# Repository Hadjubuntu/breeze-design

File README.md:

# breeze-design
Breeze design documents

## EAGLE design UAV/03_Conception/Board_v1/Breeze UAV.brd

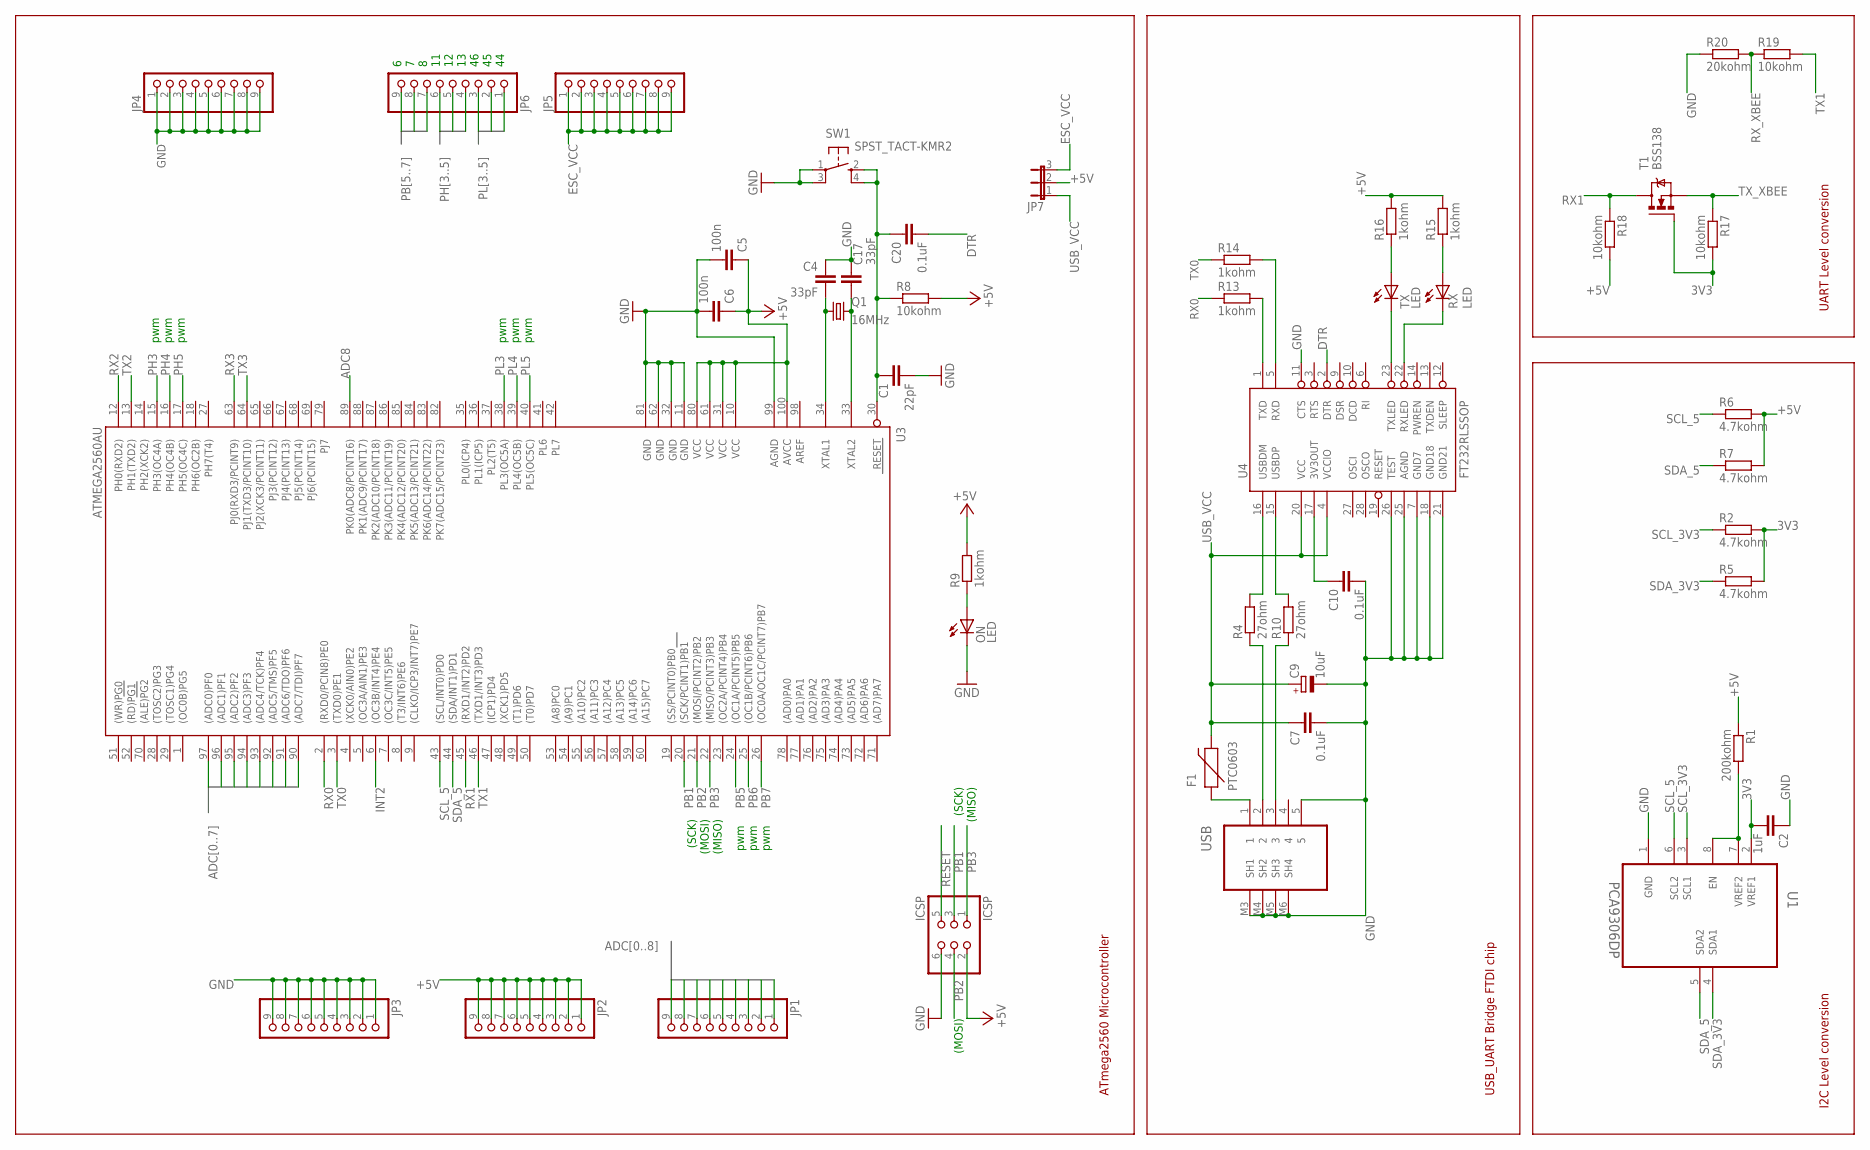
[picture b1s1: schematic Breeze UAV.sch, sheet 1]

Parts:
C1: 22pF; C0402
C2: 1uF; C0402
C4, C17: 33pF; C0402
C5, C6: 100n; C0402
C7, C10, C20: 0.1uF; C0402
C9: 10uF; SMC_A
F1: PTC0603; 0603
ICSP: ICSP; 2X03
JP1, JP2, JP3, JP4, JP5, JP6: PINHD-1X9; 1X09
JP7: JP2E; JP2
ON: LED; CHIPLED_0603
Q1: 16MHz; CTS406
R1: 200kohm; R0402
R2, R5, R6, R7: 4.7kohm; R0402
R4, R10: 27ohm; R0402
R8, R17, R18, R19: 10kohm; R0402
R9, R13, R14, R15, R16: 1kohm; R0402
R20: 20kohm; R0402
RX: LED; CHIPLED_0603
SW1: SPST_TACT-KMR2; KMR2
T1: BSS138; SOT23
TX: LED; CHIPLED_0603
U1: PCA9306DP; SOP65P490X110-8N
U3: ATMEGA2560AU; TQFP100
U4: FT232RLSSOP; SSOP28DB
USB: 47346-0001; MOLEX_47346-0001

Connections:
3V3: C2.2, R2.2, R5.2, R17.2, T1.1 (G), U1.2 (VREF1); also elsewhere on the board
+5V: C5.1, C6.1, ICSP.2, JP2.1, JP2.2, JP2.3, JP2.4, JP2.5, JP2.6, JP2.7, JP2.8, JP2.9, JP7.2, R1.1, R6.2, R7.2, R8.2, R9.2, R15.2, R16.2, R18.2, U3.10 (VCC), U3.31 (VCC1), U3.61 (VCC2), U3.80 (VCC3), U3.100 (AVCC); also elsewhere on the board
ADC0: JP1.1, U3.97 ((ADC0)PF0)
ADC1: JP1.2, U3.96 ((ADC1)PF1)
ADC2: JP1.3, U3.95 ((ADC2)PF2)
ADC3: JP1.4, U3.94 ((ADC3)PF3)
ADC4: JP1.5, U3.93 ((ADC4/TCK)PF4)
ADC5: JP1.6, U3.92 ((ADC5/TMS)PF5)
ADC6: JP1.7, U3.91 ((ADC6/TDO)PF6)
ADC7: JP1.8, U3.90 ((ADC7/TDI)PF7)
ADC8: JP1.9, U3.89 (PK0(ADC8/PCINT16))
DTR: C20.2, U4.2 (DTR)
ESC_VCC: JP5.1, JP5.2, JP5.3, JP5.4, JP5.5, JP5.6, JP5.7, JP5.8, JP5.9, JP7.3
GND: C1.2, C2.1, C4.1, C5.2, C6.2, C7.2, C9.-, C10.2, C17.2, ICSP.6, JP3.1, JP3.2, JP3.3, JP3.4, JP3.5, JP3.6, JP3.7, JP3.8, JP3.9, JP4.1, JP4.2, JP4.3, JP4.4, JP4.5, JP4.6, JP4.7, JP4.8, JP4.9, ON.C, R20.1, SW1.1, SW1.3 (P1), U1.1 (GND), U3.11 (GND), U3.32 (GND1), U3.62 (GND2), U3.81 (GND3), U3.99 (AGND), U4.7 (GND7), U4.11 (CTS), U4.18 (GND18), U4.21 (GND21), U4.25 (AGND), U4.26 (TEST), USB.5, USB.M3 (SH1), USB.M4 (SH2), USB.M5 (SH3), USB.M6 (SH4); also elsewhere on the board
INT2: U3.6 ((OC3B/INT4)PE4); also elsewhere on the board
M8RXD: R13.2, U4.1 (TXD)
unnamed: R1.2, U1.7 (VREF2), U1.8 (EN)
unnamed: ON.A, R9.1
unnamed: R4.1, USB.2
unnamed: R10.1, USB.3
unnamed: R14.2, U4.5 (RXD)
unnamed: R4.2, U4.16 (USBDM)
unnamed: R10.2, U4.15 (USBDP)
unnamed: R16.1, TX.A
unnamed: R15.1, RX.A
unnamed: RX.C, U4.22 (RXLED)
unnamed: C10.1, U4.17 (3V3OUT)
PB1: ICSP.3, U3.20 ((SCK/PCINT1)PB1)
PB2: ICSP.4, U3.21 ((MOSI/PCINT2)PB2)
PB3: ICSP.1, U3.22 ((MISO/PCINT3)PB3)
PB5: JP6.7, U3.24 ((OC1A/PCINT5)PB5)
PB6: JP6.8, U3.25 ((OC1B/PCINT6)PB6)
PB7: JP6.9, U3.26 ((OC0A/OC1C/PCINT7)PB7)
PH3: JP6.4, U3.15 (PH3(OC4A))
PH4: JP6.5, U3.16 (PH4(OC4B))
PH5: JP6.6, U3.17 (PH5(OC4C))
PL3: JP6.3, U3.38 (PL3(OC5A))
PL4: JP6.2, U3.39 (PL4(OC5B))
PL5: JP6.1, U3.40 (PL5(OC5C))
RESET: C1.1, C20.1, ICSP.5, R8.1, SW1.2 (S), SW1.4 (S1), U3.30 (RESET)
RX0: R13.1, U3.2 ((RXD0/PCIN8)PE0)
RX1: R18.1, T1.3 (D), U3.45 ((RXD1/INT2)PD2)
RX2: U3.12 (PH0(RXD2)); also elsewhere on the board
RX3: U3.63 (PJ0(RXD3/PCINT9)); also elsewhere on the board
RX_XBEE: R19.1, R20.2; also elsewhere on the board
SCL_3V3: R2.1, U1.3 (SCL1); also elsewhere on the board
SCL_5: R6.1, U1.6 (SCL2), U3.43 ((SCL/INT0)PD0); also elsewhere on the board
SDA_3V3: R5.1, U1.4 (SDA1); also elsewhere on the board
SDA_5: R7.1, U1.5 (SDA2), U3.44 ((SDA/INT1)PD1); also elsewhere on the board
TX: TX.C, U4.23 (TXLED)
TX0: R14.1, U3.3 ((TXD0)PE1)
TX1: R19.2, U3.46 ((TXD1/INT3)PD3)
TX2: U3.13 (PH1(TXD2)); also elsewhere on the board
TX3: U3.64 (PJ1(TXD3/PCINT10)); also elsewhere on the board
TX_XBEE: R17.1, T1.2 (S); also elsewhere on the board
USB_VCC: C7.1, C9.+, F1.2, JP7.1, U4.4 (VCCIO), U4.20 (VCC)
VUSB: F1.1, USB.1
XTAL1: C4.2, Q1.1, U3.34 (XTAL1)
XTAL2: C17.1, Q1.3 (2), U3.33 (XTAL2)

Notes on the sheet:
(SCK)
(MISO)
(MOSI)
pwm
I2C Level conversion
UART Level conversion
USB_UART Bridge FTDI chip
ATmega2560 Microcontroller

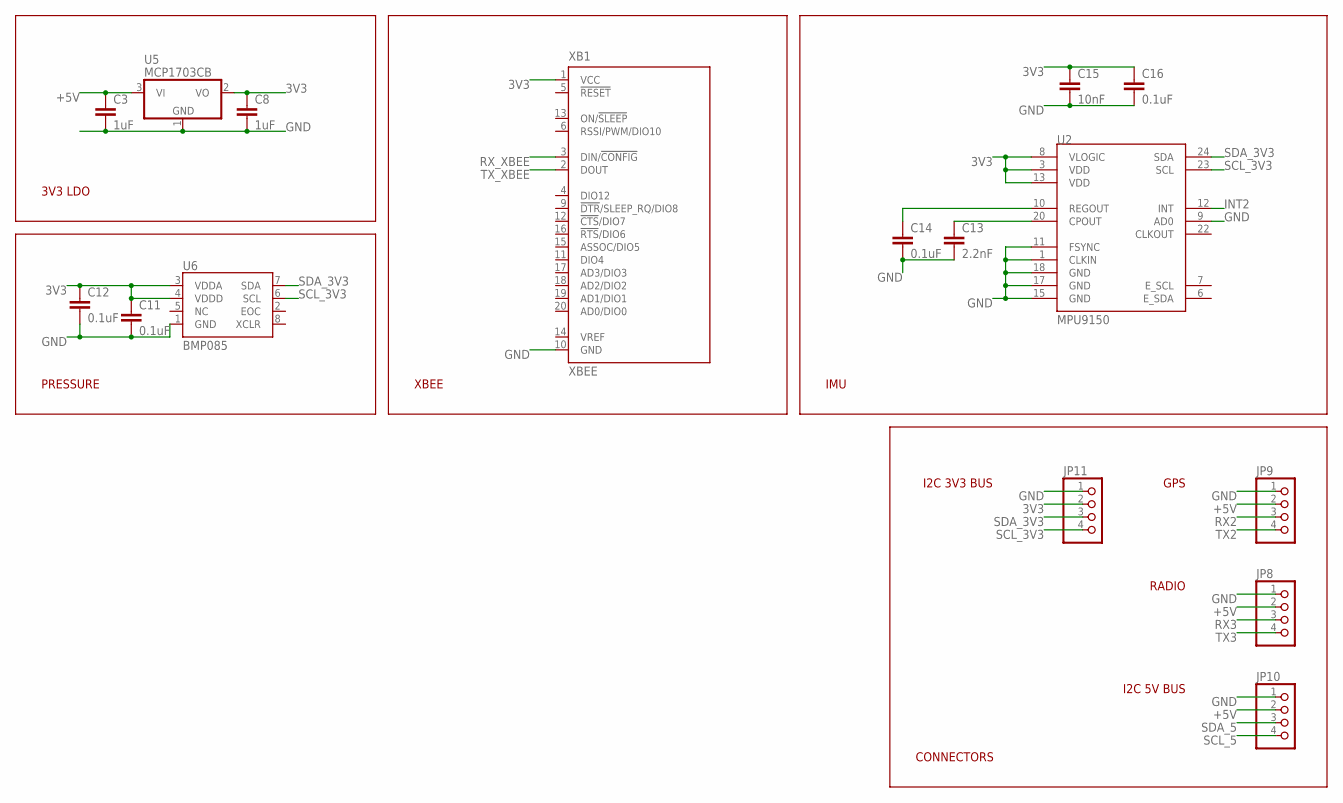
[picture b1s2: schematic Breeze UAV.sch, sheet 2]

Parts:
C3, C8: 1uF; C0402
C11, C12, C14, C16: 0.1uF; C0402
C13: 2.2nF; C0402
C15: 10nF; C0402
JP8, JP9, JP10, JP11: PINHD-1X4; 1X04
U2: MPU9150; QFN-24-NP
U5: MCP1703CB; SOT23
U6: BMP085
XB1: XBEE

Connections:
3V3: C8.1, C11.1, C12.1, C15.1, C16.1, JP11.2, U2.3 (VDD), U2.8 (VLOGIC), U2.13 (VDD), U5.2 (VO), U6.3 (VDDA), U6.4 (VDDD), XB1.1 (VCC); also elsewhere on the board
+5V: C3.1, JP8.2, JP9.2, JP10.2, U5.3 (VI); also elsewhere on the board
GND: C3.2, C8.2, C11.2, C12.2, C13.2, C14.2, C15.2, C16.2, JP8.1, JP9.1, JP10.1, JP11.1, U2.1 (CLKIN), U2.9 (AD0), U2.11 (FSYNC), U2.15 (GND), U2.17 (GND), U2.18 (GND), U5.1 (GND), U6.1 (GND), XB1.10 (GND); also elsewhere on the board
INT2: U2.12 (INT); also elsewhere on the board
unnamed: C13.1, U2.20 (CPOUT)
unnamed: C14.1, U2.10 (REGOUT)
RX2: JP9.3; also elsewhere on the board
RX3: JP8.3; also elsewhere on the board
RX_XBEE: XB1.3 (DIN/!CONFIG); also elsewhere on the board
SCL_3V3: JP11.4, U2.23 (SCL), U6.6 (SCL); also elsewhere on the board
SCL_5: JP10.4; also elsewhere on the board
SDA_3V3: JP11.3, U2.24 (SDA), U6.7 (SDA); also elsewhere on the board
SDA_5: JP10.3; also elsewhere on the board
TX2: JP9.4; also elsewhere on the board
TX3: JP8.4; also elsewhere on the board
TX_XBEE: XB1.2 (DOUT); also elsewhere on the board

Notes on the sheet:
3V3 LDO
PRESSURE
XBEE
IMU
CONNECTORS
RADIO
GPS
I2C 5V BUS
I2C 3V3 BUS

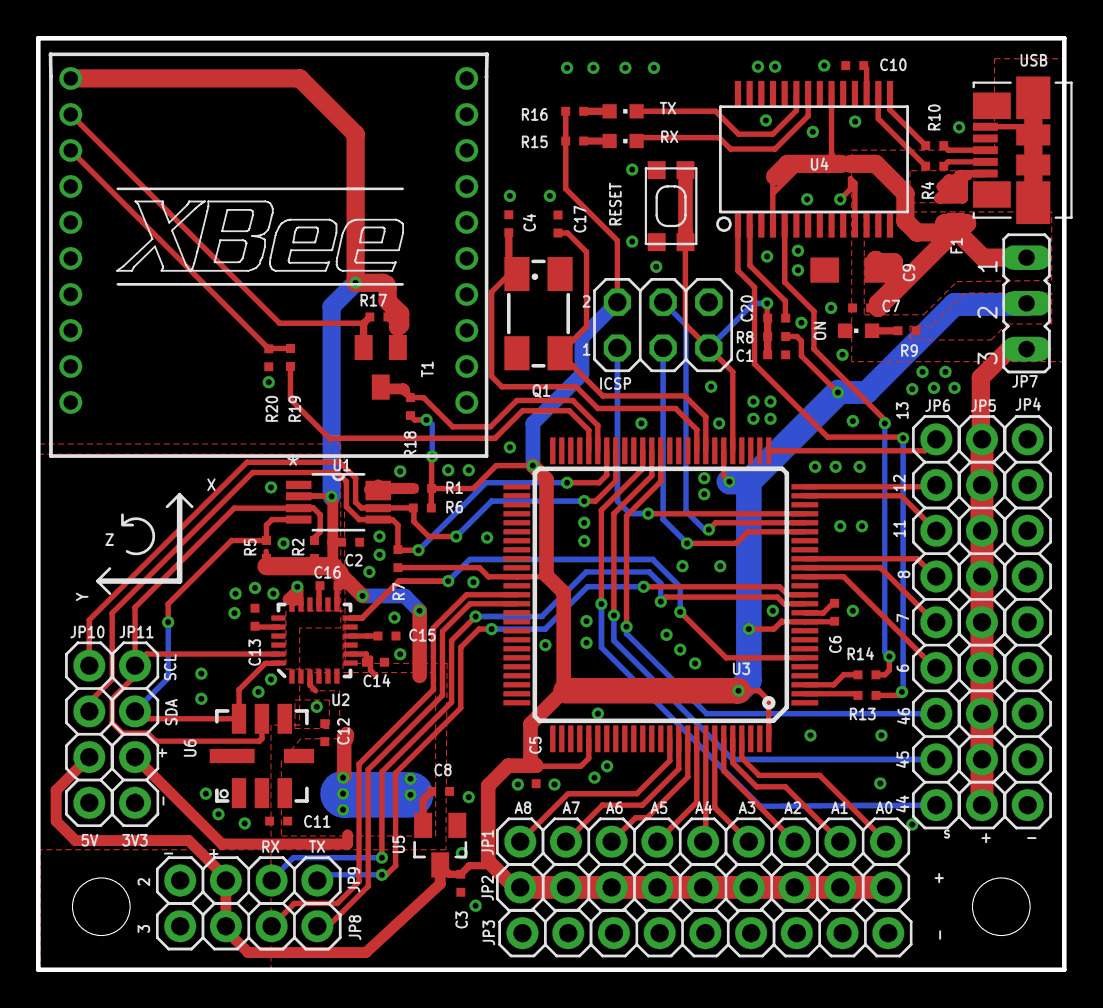
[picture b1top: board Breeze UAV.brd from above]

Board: 2 copper layers, 57.0 x 51.7 mm, 62 parts (0 on the bottom side), 61 nets.

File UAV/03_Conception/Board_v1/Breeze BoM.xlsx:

| Qty | Value | Package | Parts | Description
 | 6 | 0.1uF | C0402 | C7, C10, C11, C12, C14, C20 | CERAMIC CAPACITOR
 | 2 | 100nF | C0402 | C5, C6 | CERAMIC CAPACITOR
 | 1 | 10nF | C0402 | C16 | CERAMIC CAPACITOR
 | 1 | 10uF | SMC_A | C9 | TANTALUM CAPACITOR
 | 4 | 1uF | C0402 | C2, C3, C8, C15 | CERAMIC CAPACITOR
 | 1 | 2.2nF | C0402 | C13 | CERAMIC CAPACITOR
 | 1 | 22pF | C0402 | C1 | CERAMIC CAPACITOR
 | 2 | 33pF | C0402 | C4, C17 | CERAMIC CAPACITOR
 | 4 | 10Kohm | C0402 | R8, R17, R18, R19 | RESISTOR 1% or 5%
 | 5 | 1Kohm | C0402 | R9, R13, R14, R15, R16 | RESISTOR 1% or 5%
 | 1 | 200Kohm | C0402 | R1 | RESISTOR 1% or 5%
 | 1 | 20Kohm | C0402 | R20 | RESISTOR 1% or 5%
 | 2 | 27ohm | C0402 | R4, R10 | RESISTOR 1% or 5%
 | 4 | 4.7Kohm | C0402 | R2, R5, R6, R7 | RESISTOR 1% or 5%
 | 1 | 16MHz Crystal | CTS406 | Q1 | Mouser reff: 815-ABMM2-16-E2T
 | 3 | LED | C0603 | ON, RX, TX | LED
 | 1 | ATMEGA2560-16AU | TQFP100 | U3
 | 1 | BMP085 | LCC8 | U6
 | 1 | BSS138 | SOT23 | T1
 | 1 | MCP1703T-3302E/CB | SOT23 | U5 | 3V3 LDO
 | 1 | MPU9150 | QFN24 | U2
 | 1 | FT232RL | SSOP28 | U4
 | 1 | PCA9306DP | TSSOP8 | U1
 | 1 | PTC0603 | C0603 | F1 | 500mA resettable fuse
 | 1 | KMR223 G LFG | KMR2 | SW1 | http://www.ck-components.com/kmr-2/tactile,10572,en.html
 | 1 | USB MOLEX 47346-0001 |  | USB | 5 pos micro USB R/A SMD

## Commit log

2015-04-04 First commit doc
2015-04-05 specs pdf
2015-04-24 Commit dossier specs avt changement PC
2015-05-01 specs v2 odt file maj
2015-05-03 Maj doc specs
2015-05-16 Maj specs
2015-05-18 Spec corrections
2015-05-22 Maj docs

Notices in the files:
parts and their libraries:
SparkFun-Sensors: Licensing: Creative Commons ShareAlike 4.0 International - https://creativecommons.org/licenses/by-sa/4.0
